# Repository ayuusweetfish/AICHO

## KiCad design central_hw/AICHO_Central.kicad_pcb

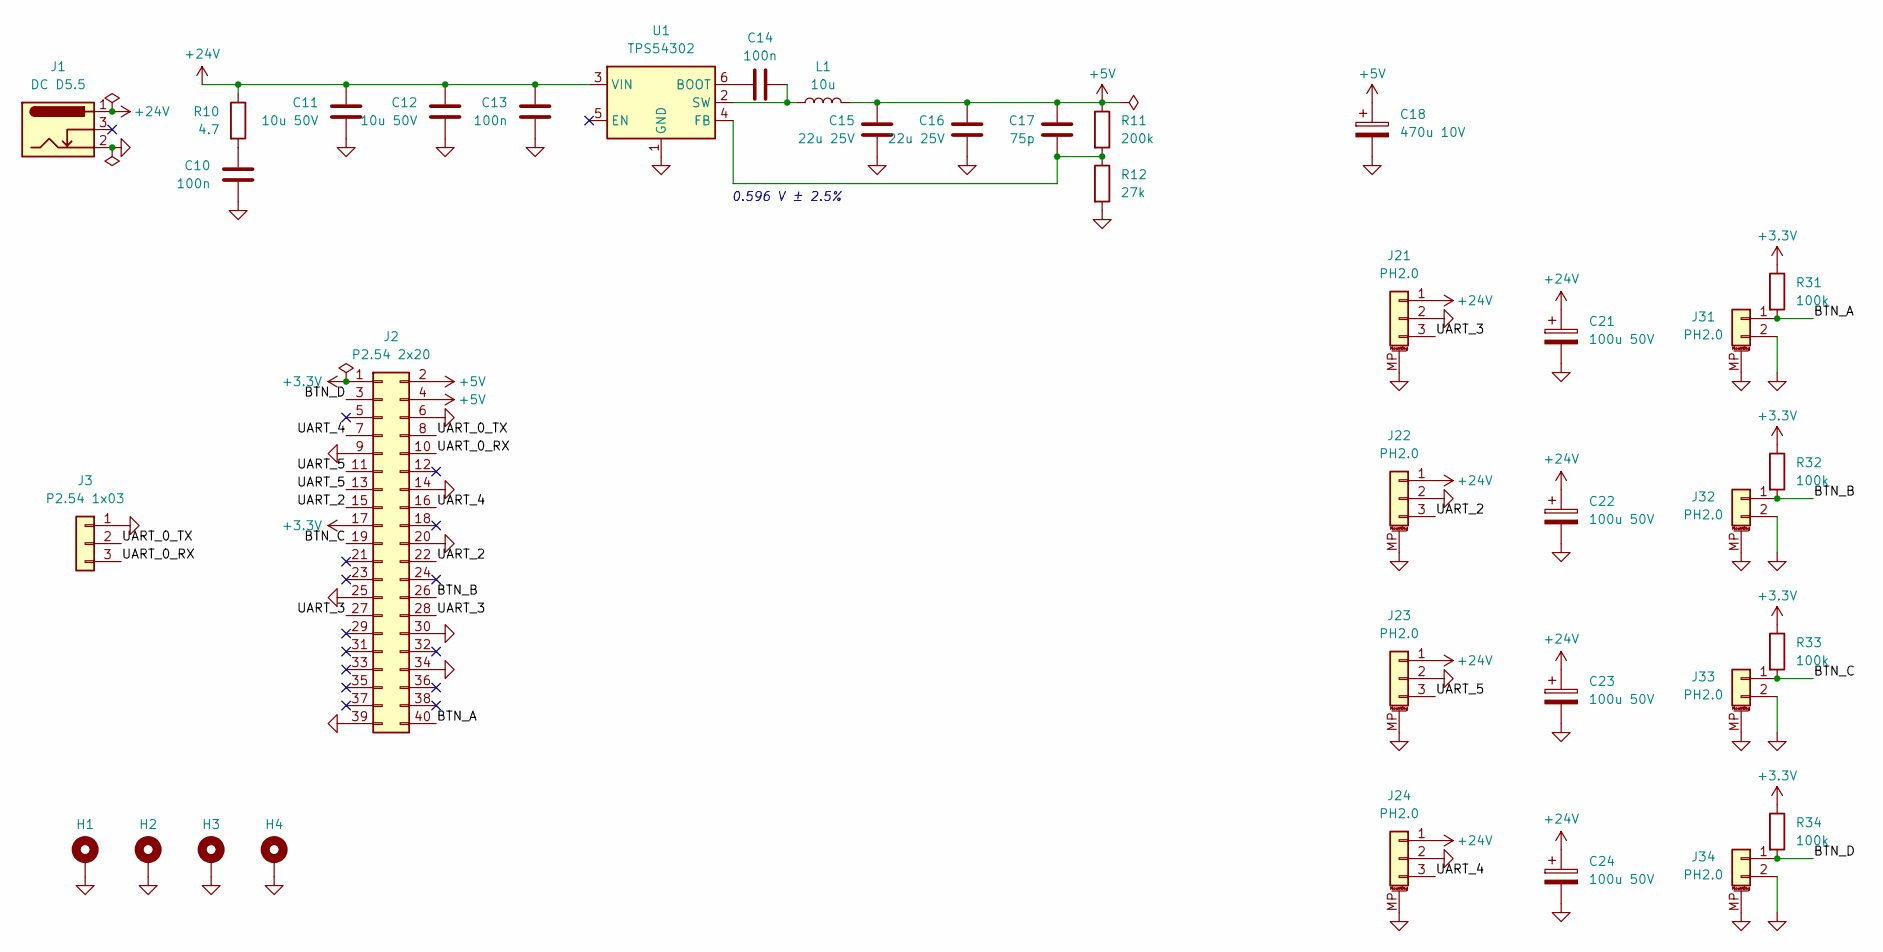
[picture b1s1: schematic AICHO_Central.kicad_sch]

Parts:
C10, C13, C14: 100n; C_0402_1005Metric
C11, C12: 10u 50V; C_0805_2012Metric
C15, C16: 22u 25V; C_0805_2012Metric
C17: 75p; C_0402_1005Metric
C18: 470u 10V; CP_Elec_6.3x7.7; Mfr PN RVT1E221M0607; LCSC PN C696188
C21, C22, C23, C24: 100u 50V; CP_Elec_6.3x7.7; Mfr PN RVT1E221M0607; LCSC PN C696188
H1, H2, H3, H4: MountingHole; MountingHole_2.2mm_M2_Pad_Via
J1: DC D5.5; BarrelJack_Kycon_KLDX-0202-xC_Horizontal
J2: P2.54 2x20; PinHeader_2x20_P2.54mm_Vertical
J3: P2.54 1x03; PinSocket_1x03_P2.54mm_Vertical
J21, J22, J23, J24: PH2.0; JST_PH_S3B-PH-SM4-TB_1x03-1MP_P2.00mm_Horizontal
J31, J32, J33, J34: PH2.0; JST_PH_S2B-PH-SM4-TB_1x02-1MP_P2.00mm_Horizontal
L1: 10u; L_Sunlord_SWPA4030S; Mfr PN SWPA4030S100MT
R10: 4.7; R_0402_1005Metric
R11: 200k; R_0402_1005Metric
R12: 27k; R_0402_1005Metric
R31, R32, R33, R34: 100k; R_0402_1005Metric
U1: TPS54302; SOT-23-6; LCSC PN C311983

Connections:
+3.3V: J2.1, J2.17, R31.1, R32.1, R33.1, R34.1
+5V: C15.1, C16.1, C17.1, C18.1, J2.2, J2.4, L1.2, R11.1
+24V: C11.1, C12.1, C13.1, C21.1, C22.1, C23.1, C24.1, J1.1, J21.1, J22.1, J23.1, J24.1, R10.1, U1.3 (VIN)
/BTN_A: J2.40, J31.1, R31.2
/BTN_B: J2.26, J32.1, R32.2
/BTN_C: J2.19, J33.1, R33.2
/BTN_D: J2.3, J34.1, R34.2
/UART_0_RX: J2.10, J3.3
/UART_0_TX: J2.8, J3.2
/UART_2: J2.15, J2.22, J22.3
/UART_3: J2.27, J2.28, J21.3
/UART_4: J2.7, J2.16, J24.3
/UART_5: J2.11, J2.13, J23.3
GND: C10.2, C11.2, C12.2, C13.2, C15.2, C16.2, C18.2, C21.2, C22.2, C23.2, C24.2, H1.1, H2.1, H3.1, H4.1, J1.2, J2.6, J2.9, J2.14, J2.20, J2.25, J2.30, J2.34, J2.39, J3.1, J21.2, J21.MP (MountPin), J22.2, J22.MP (MountPin), J23.2, J23.MP (MountPin), J24.2, J24.MP (MountPin), J31.2, J31.MP (MountPin), J32.2, J32.MP (MountPin), J33.2, J33.MP (MountPin), J34.2, J34.MP (MountPin), R12.2, U1.1 (GND)
unnamed: C10.1, R10.2
unnamed: C14.1, U1.6 (BOOT)
unnamed: C17.2, R11.2, R12.1, U1.4 (FB)
unnamed: C14.2, L1.1, U1.2 (SW)

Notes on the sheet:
0.596 V ± 2.5%

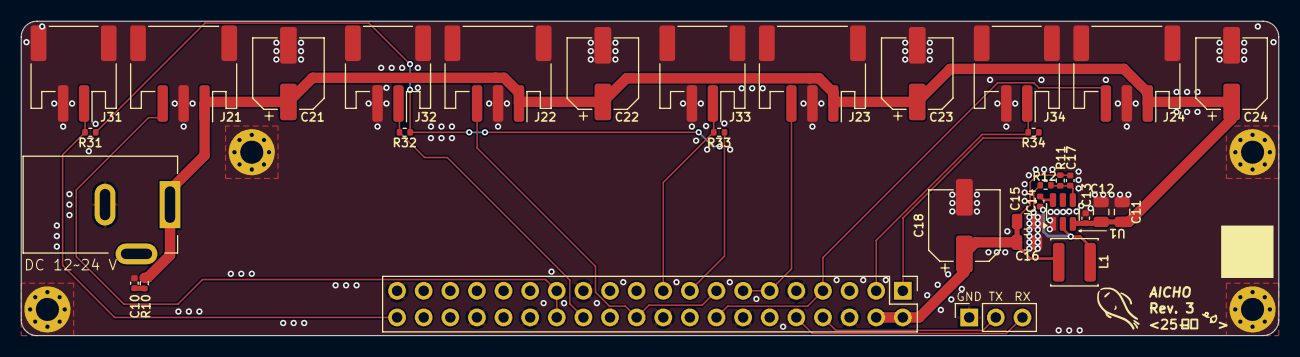
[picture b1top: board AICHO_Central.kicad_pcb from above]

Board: 2 copper layers, 120.0 x 30.0 mm, 37 parts (0 on the bottom side), 18 nets.

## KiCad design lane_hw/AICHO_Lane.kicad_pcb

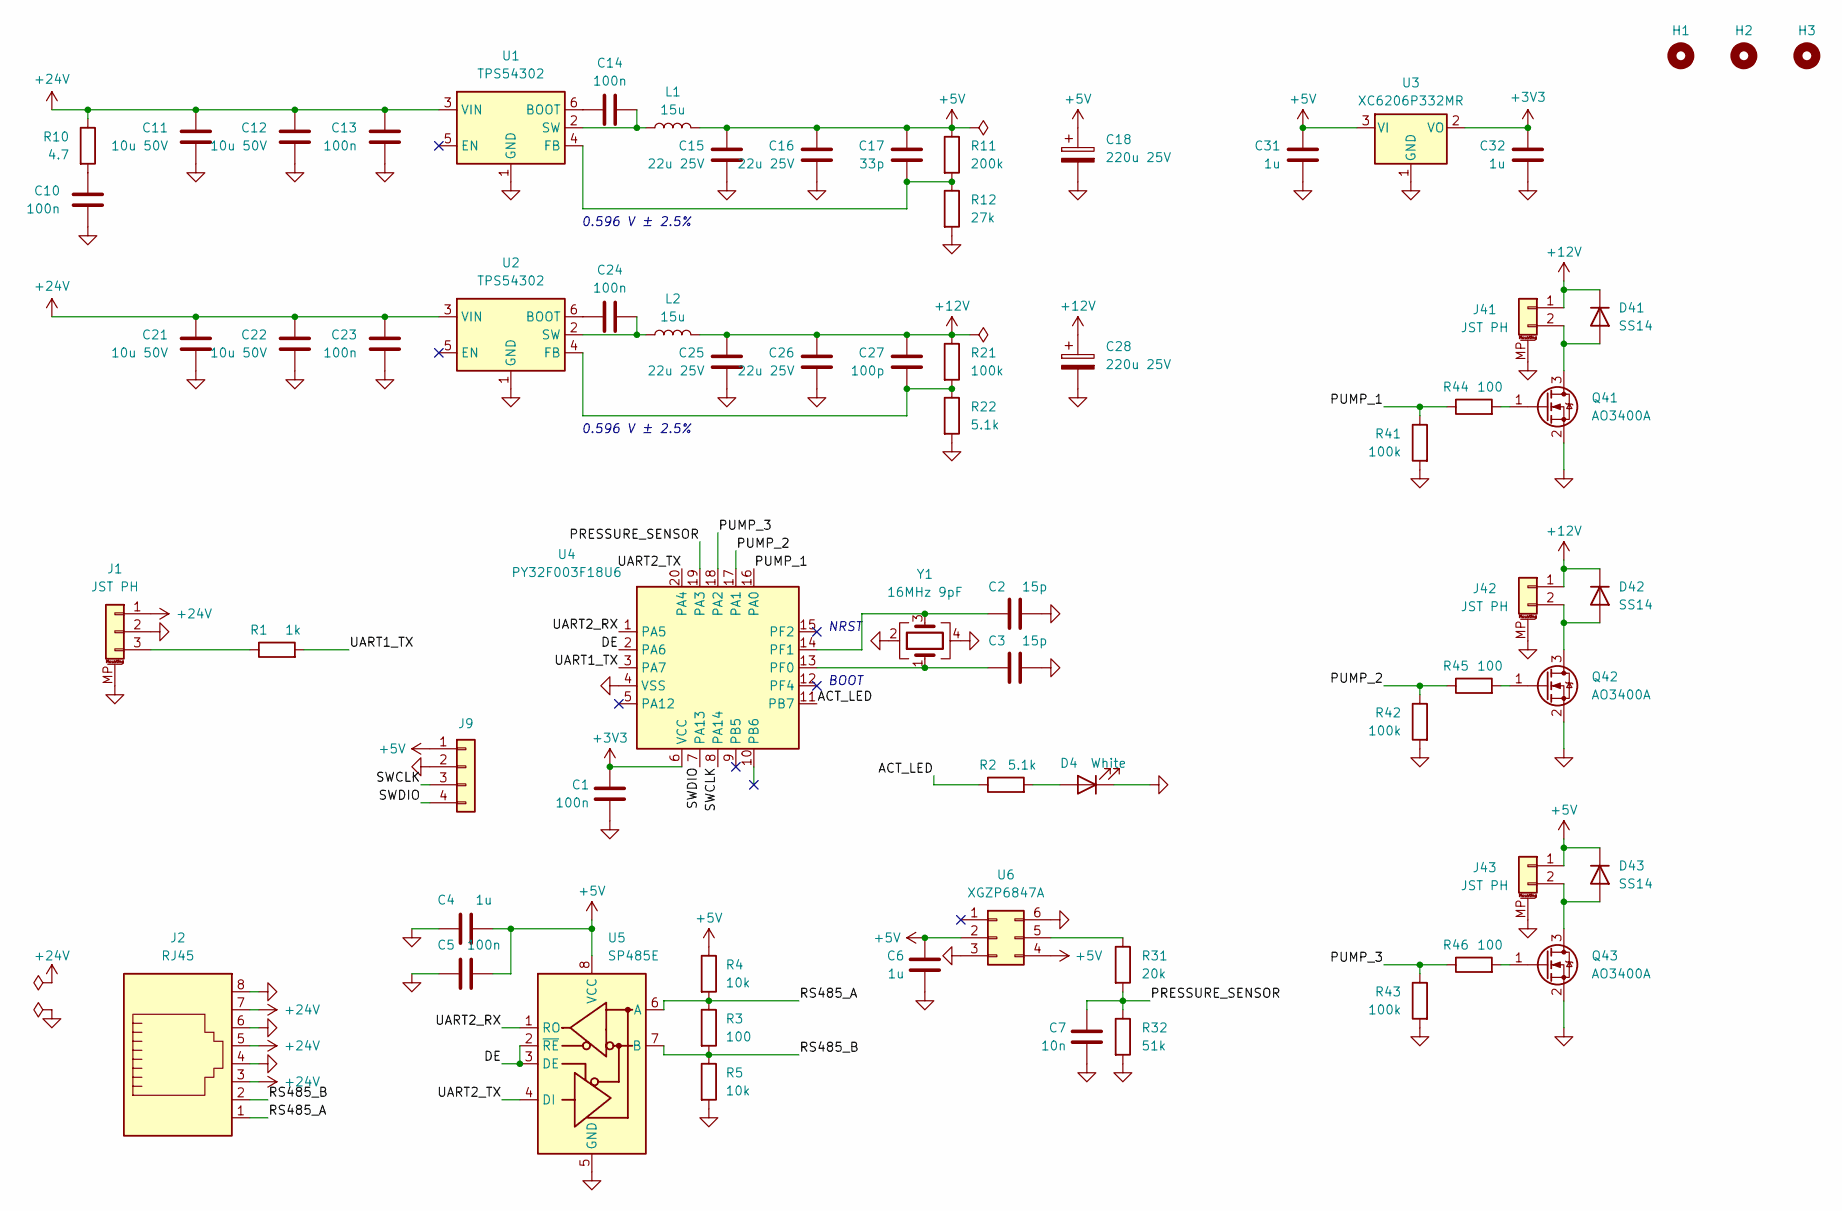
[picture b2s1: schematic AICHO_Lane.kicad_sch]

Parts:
C1, C5, C10, C13, C14, C23, C24: 100n; C_0402_1005Metric
C2, C3: 15p; C_0402_1005Metric
C4, C6, C31, C32: 1u; C_0402_1005Metric
C7: 10n; C_0402_1005Metric
C11, C12, C21, C22: 10u 50V; C_0805_2012Metric
C15, C16, C25, C26: 22u 25V; C_0805_2012Metric
C17: 33p; C_0402_1005Metric
C18, C28: 220u 25V; CP_Elec_6.3x7.7; Mfr PN RVT1E221M0607; LCSC PN C696188
C27: 100p; C_0402_1005Metric
D4: White; LED_0603_1608Metric
D41, D42, D43: SS14; D_SMA
H1, H2, H3: MountingHole; MountingHole_2.2mm_M2
J1: JST PH; JST_PH_S3B-PH-SM4-TB_1x03-1MP_P2.00mm_Horizontal; LCSC PN C7433649
J2: RJ45; RJ45_OST_PJ012-8P8CX_Vertical
J9: Conn_01x04; TestPoints_1x04_P2.00
J41, J42, J43: JST PH; JST_PH_S2B-PH-SM4-TB_1x02-1MP_P2.00mm_Horizontal; LCSC PN C7433648
L1, L2: 15u; L_Sunlord_SWPA5040S; Mfr PN PRS5040-150MT; LCSC PN C2961339
Q41, Q42, Q43: AO3400A; SOT-23
R1: 1k; R_0402_1005Metric
R2, R22: 5.1k; R_0402_1005Metric
R3, R44, R45, R46: 100; R_0402_1005Metric
R4, R5: 10k; R_0402_1005Metric
R10: 4.7; R_0402_1005Metric
R11: 200k; R_0402_1005Metric
R12: 27k; R_0402_1005Metric
R21, R41, R42, R43: 100k; R_0402_1005Metric
R31: 20k; R_0402_1005Metric
R32: 51k; R_0402_1005Metric
U1, U2: TPS54302; SOT-23-6; LCSC PN C311983
U3: XC6206P332MR; SOT-23-3; LCSC PN C5446
U4: PY32F003F18U6; QFN-20-1EP_3x3mm_P0.4mm_EP1.65x1.65mm; LCSC PN C7422665
U5: SP485E; SOIC-8_3.9x4.9mm_P1.27mm; LCSC PN C6855
U6: XGZP6847A
Y1: 16MHz 9pF; Crystal_SMD_3225-4Pin_3.2x2.5mm; Mfr PN X322516MLB4SI; LCSC PN C13738

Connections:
+3V3: C1.1, C32.1, U3.2 (VO), U4.6 (VCC)
+5V: C4.2, C5.2, C6.1, C15.1, C16.1, C17.1, C18.1, C31.1, D43.1 (K), J9.1, J43.1, L1.2, R4.1, R11.1, U3.3 (VI), U5.8 (VCC), U6.2, U6.4
+12V: C25.1, C26.1, C27.1, C28.1, D41.1 (K), D42.1 (K), J41.1, J42.1, L2.2, R21.1
+24V: C11.1, C12.1, C13.1, C21.1, C22.1, C23.1, J1.1, J2.3, J2.5, J2.7, R10.1, U1.3 (VIN), U2.3 (VIN)
/ACT_LED: R2.1, U4.11 (PB7)
/DE: U4.2 (PA6), U5.2 (~RE), U5.3 (DE)
/PRESSURE_SENSOR: C7.1, R31.2, R32.1, U4.19 (PA3)
/PUMP_1: R41.1, R44.1, U4.16 (PA0)
/PUMP_2: R42.1, R45.1, U4.17 (PA1)
/PUMP_3: R43.1, R46.1, U4.18 (PA2)
/RS485_A: J2.1, R3.1, R4.2, U5.6 (A)
/RS485_B: J2.2, R3.2, R5.1, U5.7 (B)
/SWCLK: J9.3, U4.8 (PA14)
/SWDIO: J9.4, U4.7 (PA13)
/UART1_TX: R1.2, U4.3 (PA7)
/UART2_RX: U4.1 (PA5), U5.1 (RO)
/UART2_TX: U4.20 (PA4), U5.4 (DI)
GND: C1.2, C2.2, C3.2, C4.1, C5.1, C6.2, C7.2, C10.2, C11.2, C12.2, C13.2, C15.2, C16.2, C18.2, C21.2, C22.2, C23.2, C25.2, C26.2, C28.2, C31.2, C32.2, D4.1 (K), J1.2, J1.MP (MountPin), J2.4, J2.6, J2.8, J9.2, J41.MP (MountPin), J42.MP (MountPin), J43.MP (MountPin), Q41.2 (S), Q42.2 (S), Q43.2 (S), R5.2, R12.2, R22.2, R32.2, R41.2, R42.2, R43.2, U1.1 (GND), U2.1 (GND), U3.1 (GND), U4.4 (VSS), U4.21 (PAD), U5.5 (GND), U6.3, U6.6, Y1.2, Y1.4
unnamed: C10.1, R10.2
unnamed: D4.2 (A), R2.2
unnamed: D41.2 (A), J41.2, Q41.3 (D)
unnamed: D42.2 (A), J42.2, Q42.3 (D)
unnamed: D43.2 (A), J43.2, Q43.3 (D)
unnamed: J1.3, R1.1
unnamed: Q41.1 (G), R44.2
unnamed: Q42.1 (G), R45.2
unnamed: Q43.1 (G), R46.2
unnamed: C14.1, U1.6 (BOOT)
unnamed: C17.2, R11.2, R12.1, U1.4 (FB)
unnamed: C14.2, L1.1, U1.2 (SW)
unnamed: C24.1, U2.6 (BOOT)
unnamed: C27.2, R21.2, R22.1, U2.4 (FB)
unnamed: C24.2, L2.1, U2.2 (SW)
unnamed: C3.1, U4.13 (PF0), Y1.1
unnamed: C2.1, U4.14 (PF1), Y1.3
unnamed: R31.1, U6.5

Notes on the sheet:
BOOT
NRST
0.596 V ± 2.5%

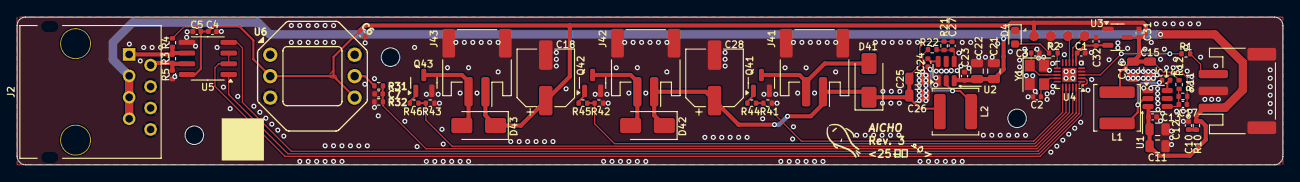
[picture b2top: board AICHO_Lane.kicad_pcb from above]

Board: 2 copper layers, 150.0 x 17.5 mm, 69 parts (0 on the bottom side), 36 nets.

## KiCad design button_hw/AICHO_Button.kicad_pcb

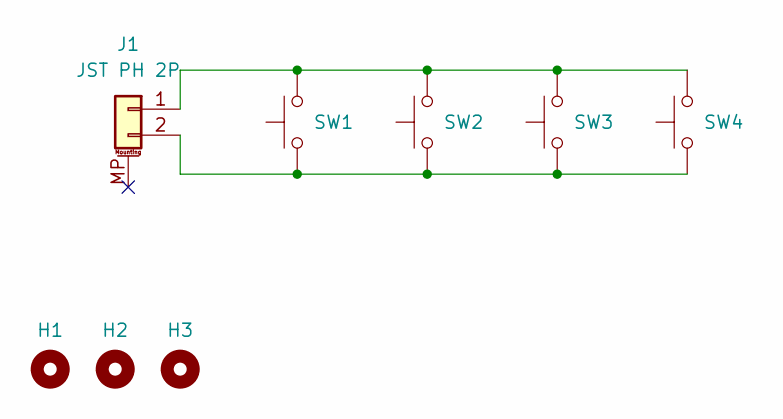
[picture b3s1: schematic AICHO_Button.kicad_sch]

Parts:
H1, H2, H3: MountingHole; MountingHole_2mm
J1: JST PH 2P; JST_PH_S2B-PH-SM4-TB_1x02-1MP_P2.00mm_Horizontal
SW1, SW2, SW3, SW4: SW_Push; SW_Cherry_MX_1.00u_Plate

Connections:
unnamed: J1.1, SW1.1, SW2.1, SW3.1, SW4.1
unnamed: J1.2, SW1.2, SW2.2, SW3.2, SW4.2

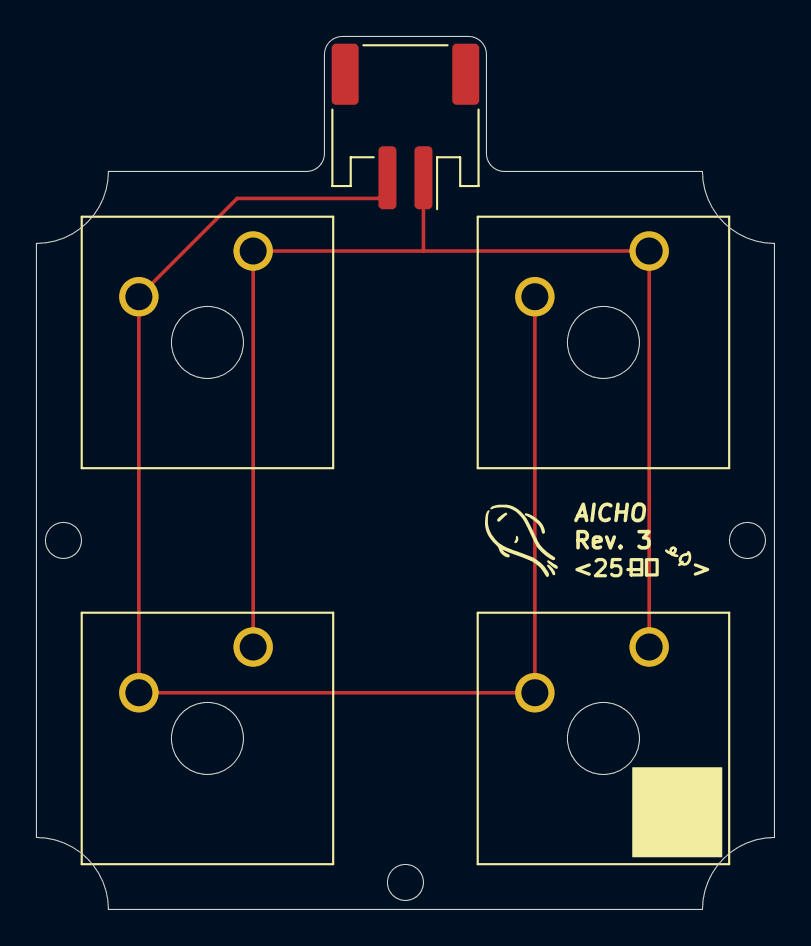
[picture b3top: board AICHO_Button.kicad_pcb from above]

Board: 2 copper layers, 41.0 x 48.5 mm, 8 parts (0 on the bottom side), 2 nets.

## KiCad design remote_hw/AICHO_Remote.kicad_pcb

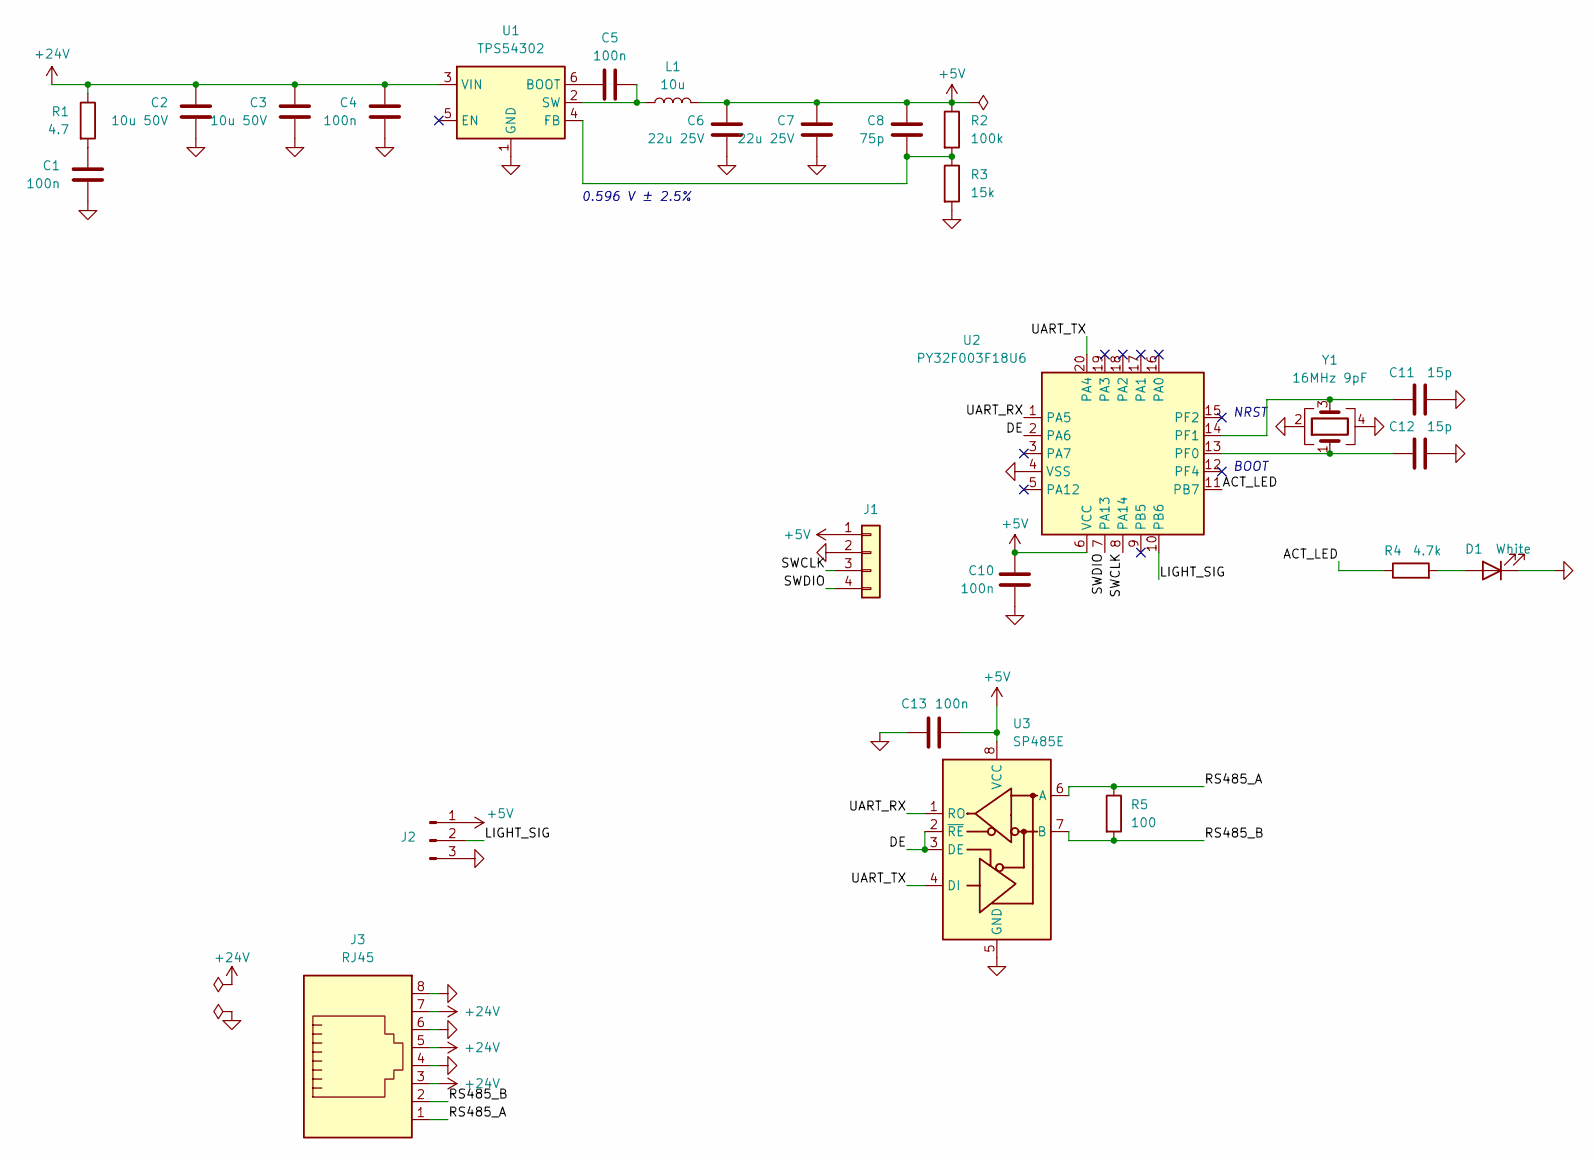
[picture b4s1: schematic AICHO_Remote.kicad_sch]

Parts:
C1, C4, C5, C10, C13: 100n; C_0402_1005Metric
C2, C3: 10u 50V; C_0805_2012Metric
C6, C7: 22u 25V; C_0805_2012Metric
C8: 75p; C_0402_1005Metric
C11, C12: 15p; C_0402_1005Metric
D1: White; LED_0603_1608Metric
J1: Conn_01x04; TestPoints_1x04_P2.00
J2: Conn_01x03_Pin; PinHeader_1x03_P2.54mm_Vertical
J3: RJ45; RJ45_OST_PJ012-8P8CX_Vertical
L1: 10u; L_Sunlord_SWPA4030S; Mfr PN SWPA4030S100MT; LCSC PN C38117
R1: 4.7; R_0402_1005Metric
R2: 100k; R_0402_1005Metric
R3: 15k; R_0402_1005Metric
R4: 4.7k; R_0402_1005Metric
R5: 100; R_0402_1005Metric
U1: TPS54302; SOT-23-6; LCSC PN C311983
U2: PY32F003F18U6; QFN-20-1EP_3x3mm_P0.4mm_EP1.65x1.65mm; LCSC PN C7422665
U3: SP485E; SOIC-8_3.9x4.9mm_P1.27mm; LCSC PN C6855
Y1: 16MHz 9pF; Crystal_SMD_3225-4Pin_3.2x2.5mm; Mfr PN X322516MLB4SI; LCSC PN C13738

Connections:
+5V: C6.1, C7.1, C8.1, C10.1, C13.2, J1.1, J2.1, L1.2, R2.1, U2.6 (VCC), U3.8 (VCC)
+24V: C2.1, C3.1, C4.1, J3.3, J3.5, J3.7, R1.1, U1.3 (VIN)
/ACT_LED: R4.1, U2.11 (PB7)
/DE: U2.2 (PA6), U3.2 (~RE), U3.3 (DE)
/LIGHT_SIG: J2.2, U2.10 (PB6)
/RS485_A: J3.1, R5.1, U3.6 (A)
/RS485_B: J3.2, R5.2, U3.7 (B)
/SWCLK: J1.3, U2.8 (PA14)
/SWDIO: J1.4, U2.7 (PA13)
/UART_RX: U2.1 (PA5), U3.1 (RO)
/UART_TX: U2.20 (PA4), U3.4 (DI)
GND: C1.2, C2.2, C3.2, C4.2, C6.2, C7.2, C10.2, C11.2, C12.2, C13.1, D1.1 (K), J1.2, J2.3, J3.4, J3.6, J3.8, R3.2, U1.1 (GND), U2.4 (VSS), U2.21 (PAD), U3.5 (GND), Y1.2, Y1.4
unnamed: C1.1, R1.2
unnamed: D1.2 (A), R4.2
unnamed: C5.1, U1.6 (BOOT)
unnamed: C8.2, R2.2, R3.1, U1.4 (FB)
unnamed: C5.2, L1.1, U1.2 (SW)
unnamed: C12.1, U2.13 (PF0), Y1.1
unnamed: C11.1, U2.14 (PF1), Y1.3

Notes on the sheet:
BOOT
NRST
0.596 V ± 2.5%

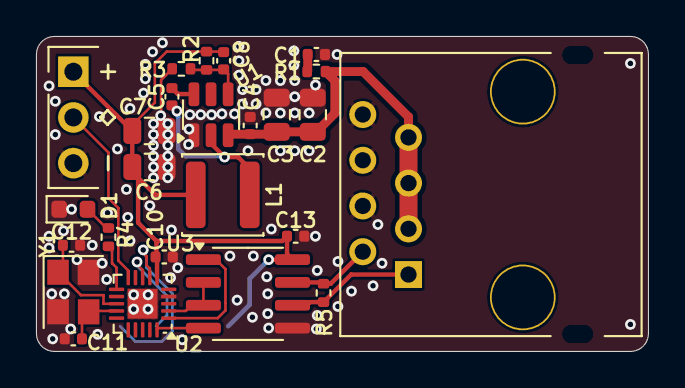
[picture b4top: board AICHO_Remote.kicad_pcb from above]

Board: 2 copper layers, 34.0 x 17.5 mm, 26 parts (1 on the bottom side), 19 nets.

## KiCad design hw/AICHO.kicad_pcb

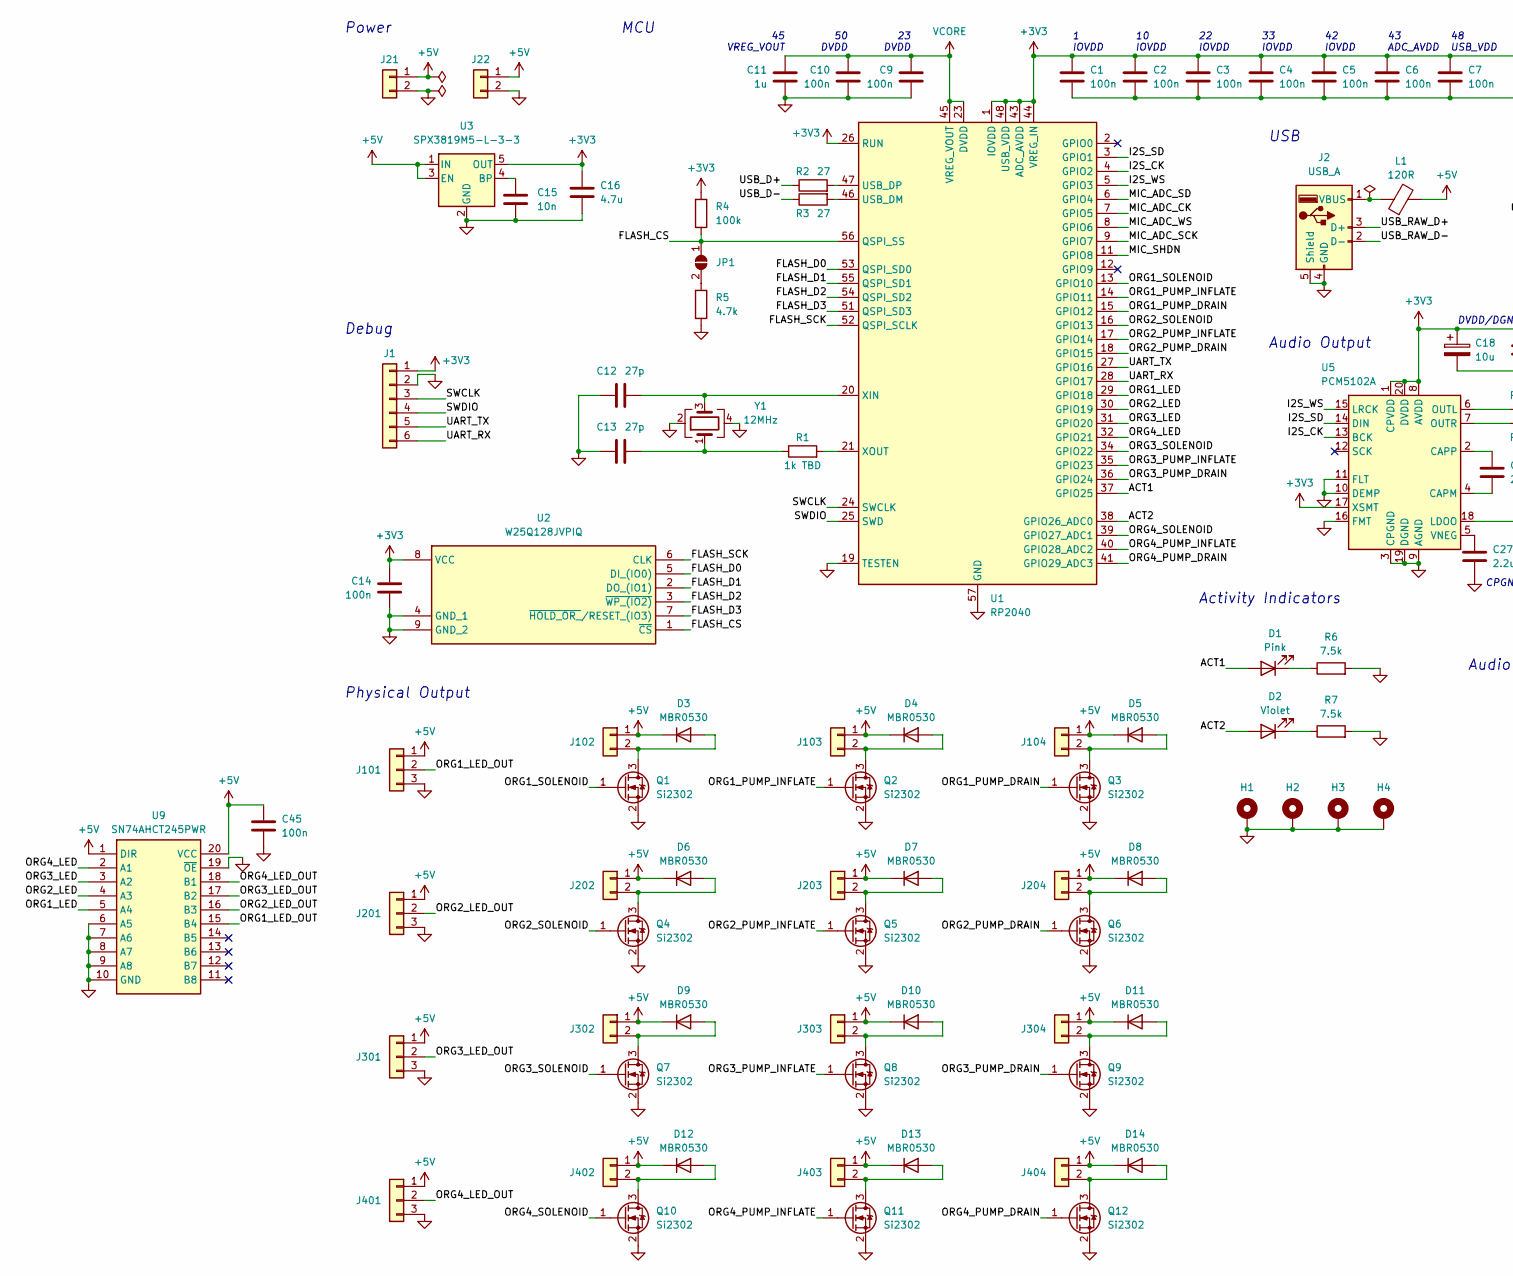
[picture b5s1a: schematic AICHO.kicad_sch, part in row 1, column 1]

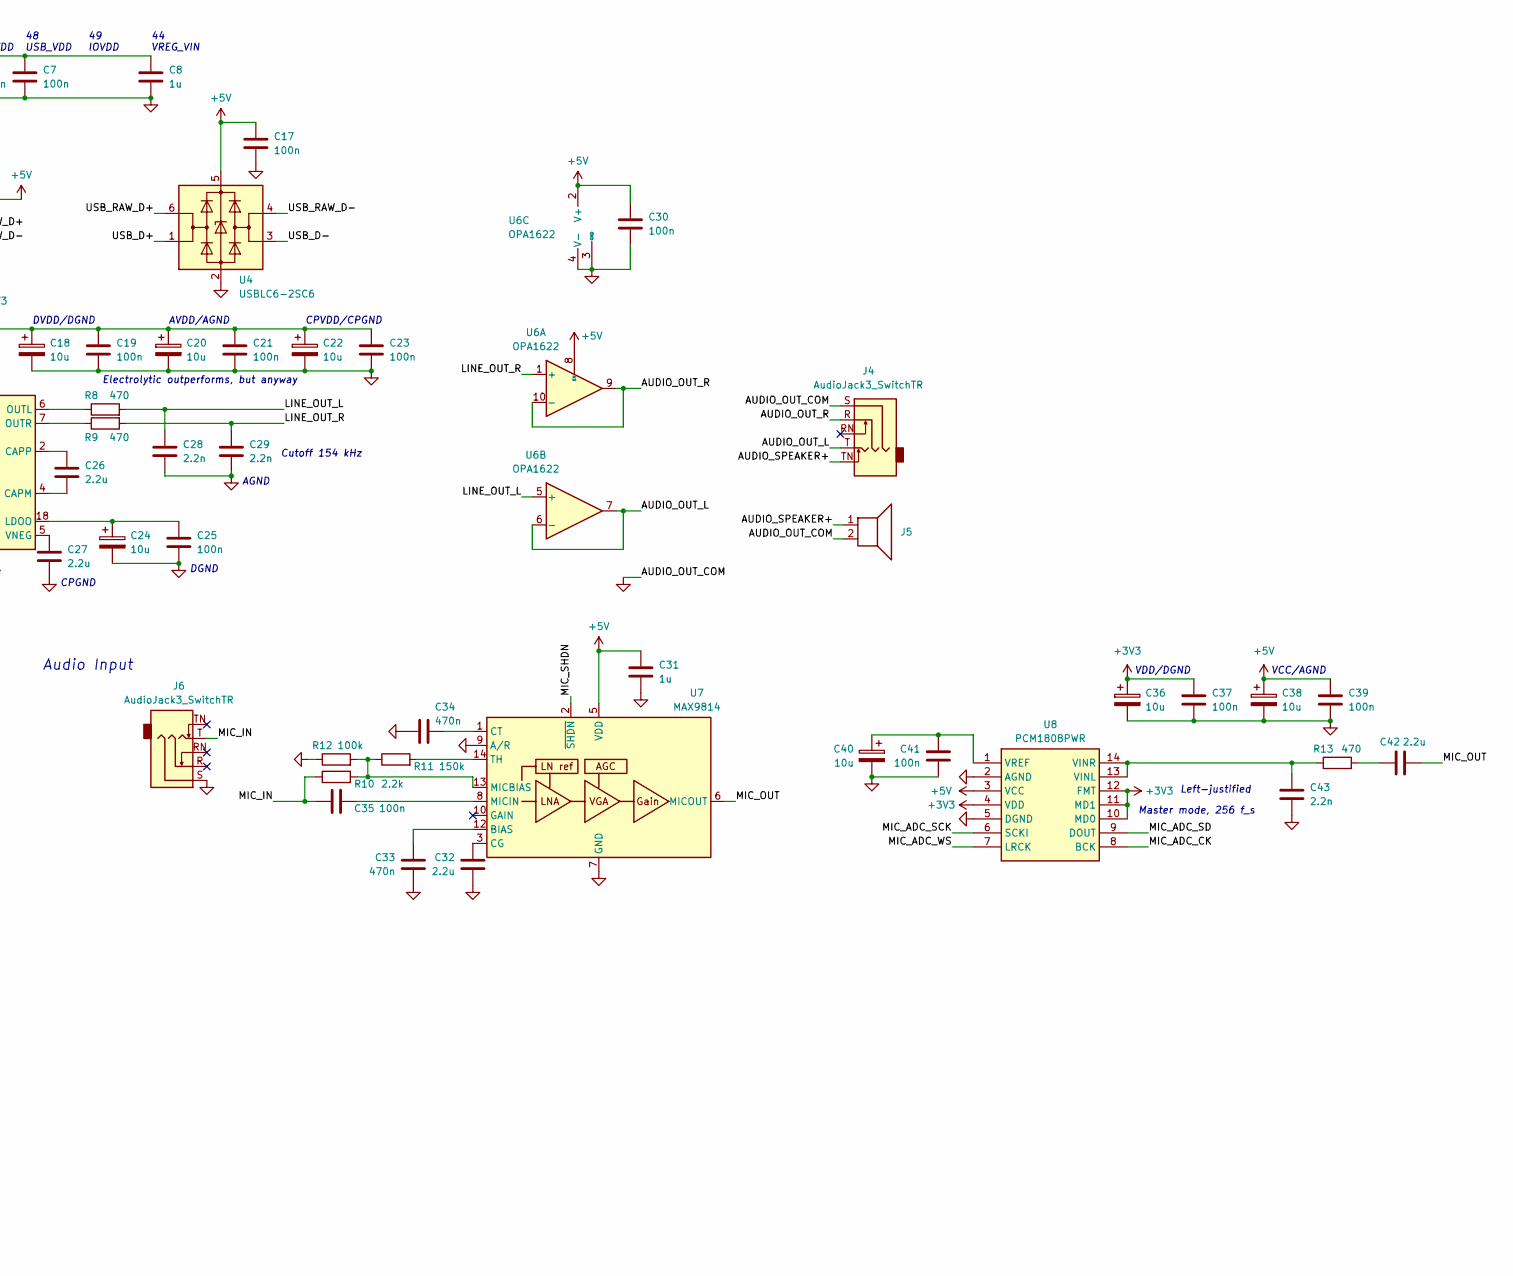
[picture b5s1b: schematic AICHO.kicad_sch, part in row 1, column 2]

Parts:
C1, C2, C3, C4, C5, C6, C7, C9, C10, C14, C17, C19, C21, C23, C25, C30, C35, C37, C39, C41, C45: 100n; C_0402_1005Metric
C8, C11, C31: 1u; C_0402_1005Metric
C12, C13: 27p; C_0402_1005Metric
C15: 10n; C_0603_1608Metric
C16: 4.7u; C_0603_1608Metric
C18, C20, C22, C24, C36, C38, C40: 10u; C_0603_1608Metric
C26, C27, C32, C42: 2.2u; C_0402_1005Metric
C28, C29, C43: 2.2n; C_0402_1005Metric
C33, C34: 470n; C_0402_1005Metric
D1: Pink; LED_0603_1608Metric
D2: Violet; LED_0603_1608Metric
D3, D4, D5, D6, D7, D8, D9, D10, D11, D12, D13, D14: MBR0530; D_SOD-123
H1, H2, H3, H4: MountingHole_Pad; MountingHole_2.5mm_Pad_Via
J1: Conn_01x06; TestPoints_1x06_P2.0
J2: USB_A; USB_A_CNCTech_1001-011-01101_Horizontal
J4, J6: AudioJack3_SwitchTR; Jack_3.5mm_CUI_SJ1-3525N_Horizontal
J5: Speaker; PinHeader_1x02_P2.54mm_Vertical
J21, J22, J102, J103, J104, J202, J203, J204, J302, J303, J304, J402, J403, J404: Conn_01x02; PinHeader_1x02_P2.54mm_Vertical
J101, J201, J301, J401: Conn_01x03; PinHeader_1x03_P2.54mm_Vertical
JP1: SolderJumper_2_Open; SolderJumper-2_P1.3mm_Open_RoundedPad1.0x1.5mm
L1: 120R; L_0805_2012Metric
Q1, Q2, Q3, Q4, Q5, Q6, Q7, Q8, Q9, Q10, Q11, Q12: Si2302; SOT-23
R1: 1k TBD; R_0603_1608Metric
R2, R3: 27; R_0603_1608Metric
R4: 100k; R_0603_1608Metric
R5: 4.7k; R_0603_1608Metric
R6, R7: 7.5k; R_0603_1608Metric
R8, R9, R13: 470; R_0402_1005Metric
R10: 2.2k; R_0402_1005Metric
R11: 150k; R_0402_1005Metric
R12: 100k; R_0402_1005Metric
U1: RP2040; QFN-56-1EP_7x7mm_P0.4mm_EP3.2x3.2mm
U2: W25Q128JVPIQ; SON127P600X500X80-9N-D; Manufacturer_Part_Number W25Q128JVPIQ; Mouser Part Number 454-W25Q128JVPIQ
U3: SPX3819M5-L-3-3; SOT-23-5
U4: USBLC6-2SC6; SOT-23-6
U5: PCM5102A; TSSOP-20_4.4x6.5mm_P0.65mm
U6: OPA1622; Texas_S-PVSON-N10
U7: MAX9814; DFN-14-1EP_3x3mm_P0.4mm_EP1.78x2.35mm
U8: PCM1808PWR; Manufacturer_Part_Number PCM1808PWR; Mouser Part Number 595-PCM1808PWR
U9: SN74AHCT245PWR; SOP65P640X120-20N; Manufacturer_Part_Number SN74AHCT245PWR; Mouser Part Number 595-SN74AHCT245PWR
Y1: 12MHz; Crystal_SMD_3225-4Pin_3.2x2.5mm

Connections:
+3V3: C1.1, C2.1, C3.1, C4.1, C5.1, C6.1, C7.1, C8.1, C14.1, C16.1, C18.1, C19.1, C20.1, C21.1, C22.1, C23.1, C36.1, C37.1, J1.1, R4.2, U1.1 (IOVDD), U1.10 (IOVDD), U1.22 (IOVDD), U1.26 (RUN), U1.33 (IOVDD), U1.42 (IOVDD), U1.43 (ADC_AVDD), U1.44 (VREG_IN), U1.48 (USB_VDD), U1.49 (IOVDD), U2.8 (VCC), U3.5 (OUT), U5.1 (CPVDD), U5.8 (AVDD), U5.17 (XSMT), U5.20 (DVDD), U8.4 (VDD), U8.10 (MD0), U8.11 (MD1), U8.12 (FMT)
+5V: C17.1, C30.1, C31.1, C38.1, C39.1, C45.1, D3.1 (K), D4.1 (K), D5.1 (K), D6.1 (K), D7.1 (K), D8.1 (K), D9.1 (K), D10.1 (K), D11.1 (K), D12.1 (K), D13.1 (K), D14.1 (K), J21.1, J22.1, J101.1, J102.1, J103.1, J104.1, J201.1, J202.1, J203.1, J204.1, J301.1, J302.1, J303.1, J304.1, J401.1, J402.1, J403.1, J404.1, L1.2, U3.1 (IN), U3.3 (EN), U4.5 (VBUS), U6.2 (V+), U6.8 (EN), U7.5 (VDD), U8.3 (VCC), U9.1 (DIR), U9.20 (VCC)
/ACT1: D1.2 (A), U1.37 (GPIO25)
/ACT2: D2.2 (A), U1.38 (GPIO26_ADC0)
/AUDIO_OUT_L: J4.T, U6.6 (-), U6.7
/AUDIO_OUT_R: J4.R, U6.9, U6.10 (-)
/AUDIO_SPEAKER+: J4.TN, J5.1
/FLASH_CS: JP1.1 (A), R4.1, U1.56 (QSPI_SS), U2.1 (~CS)
/FLASH_D0: U1.53 (QSPI_SD0), U2.5 (DI_(IO0))
/FLASH_D1: U1.55 (QSPI_SD1), U2.2 (DO_(IO1))
/FLASH_D2: U1.54 (QSPI_SD2), U2.3 (~WP_(IO2))
/FLASH_D3: U1.51 (QSPI_SD3), U2.7 (~HOLD_OR_/RESET_(IO3))
/FLASH_SCK: U1.52 (QSPI_SCLK), U2.6 (CLK)
/I2S_CK: U1.4 (GPIO2), U5.13 (BCK)
/I2S_SD: U1.3 (GPIO1), U5.14 (DIN)
/I2S_WS: U1.5 (GPIO3), U5.15 (LRCK)
/LINE_OUT_L: C28.1, R8.2, U6.5 (+)
/LINE_OUT_R: C29.1, R9.2, U6.1 (+)
/MIC_ADC_CK: U1.7 (GPIO5), U8.8 (BCK)
/MIC_ADC_SCK: U1.9 (GPIO7), U8.6 (SCKI)
/MIC_ADC_SD: U1.6 (GPIO4), U8.9 (DOUT)
/MIC_ADC_WS: U1.8 (GPIO6), U8.7 (LRCK)
/MIC_IN: C35.1, J6.T, R10.1
/MIC_OUT: C42.2, U7.6 (MICOUT)
/MIC_SHDN: U1.11 (GPIO8), U7.2 (~SHDN)
/ORG1_LED: U1.29 (GPIO18), U9.5 (A4)
/ORG1_LED_OUT: J101.2, U9.15 (B4)
/ORG1_PUMP_DRAIN: Q3.1 (G), U1.15 (GPIO12)
/ORG1_PUMP_INFLATE: Q2.1 (G), U1.14 (GPIO11)
/ORG1_SOLENOID: Q1.1 (G), U1.13 (GPIO10)
/ORG2_LED: U1.30 (GPIO19), U9.4 (A3)
/ORG2_LED_OUT: J201.2, U9.16 (B3)
/ORG2_PUMP_DRAIN: Q6.1 (G), U1.18 (GPIO15)
/ORG2_PUMP_INFLATE: Q5.1 (G), U1.17 (GPIO14)
/ORG2_SOLENOID: Q4.1 (G), U1.16 (GPIO13)
/ORG3_LED: U1.31 (GPIO20), U9.3 (A2)
/ORG3_LED_OUT: J301.2, U9.17 (B2)
/ORG3_PUMP_DRAIN: Q9.1 (G), U1.36 (GPIO24)
/ORG3_PUMP_INFLATE: Q8.1 (G), U1.35 (GPIO23)
/ORG3_SOLENOID: Q7.1 (G), U1.34 (GPIO22)
/ORG4_LED: U1.32 (GPIO21), U9.2 (A1)
/ORG4_LED_OUT: J401.2, U9.18 (B1)
/ORG4_PUMP_DRAIN: Q12.1 (G), U1.41 (GPIO29_ADC3)
/ORG4_PUMP_INFLATE: Q11.1 (G), U1.40 (GPIO28_ADC2)
/ORG4_SOLENOID: Q10.1 (G), U1.39 (GPIO27_ADC1)
/SWCLK: J1.3, U1.24 (SWCLK)
/SWDIO: J1.4, U1.25 (SWD)
/UART_RX: J1.6, U1.28 (GPIO17)
/UART_TX: J1.5, U1.27 (GPIO16)
/USB_D+: R2.1, U4.1 (I/O1)
/USB_D-: R3.1, U4.3 (I/O2)
/USB_RAW_D+: J2.3 (D+), U4.6 (I/O1)
/USB_RAW_D-: J2.2 (D-), U4.4 (I/O2)
GND: C1.2, C2.2, C3.2, C4.2, C5.2, C6.2, C7.2, C8.2, C9.2, C10.2, C11.2, C12.1, C13.1, C14.2, C15.2, C16.2, C17.2, C18.2, C19.2, C20.2, C21.2, C22.2, C23.2, C24.2, C25.2, C27.2, C28.2, C29.2, C30.2, C31.2, C32.2, C33.2, C34.2, C36.2, C37.2, C38.2, C39.2, C40.2, C41.2, C43.2, C45.2, H1.1, H2.1, H3.1, H4.1, J1.2, J2.4 (GND), J2.5 (Shield), J4.S, J5.2, J6.S, J21.2, J22.2, J101.3, J201.3, J301.3, J401.3, Q1.2 (S), Q2.2 (S), Q3.2 (S), Q4.2 (S), Q5.2 (S), Q6.2 (S), Q7.2 (S), Q8.2 (S), Q9.2 (S), Q10.2 (S), Q11.2 (S), Q12.2 (S), R5.1, R6.2, R7.2, R12.1, U1.19 (TESTEN), U1.57 (GND), U2.4 (GND_1), U2.9 (GND_2), U3.2 (GND), U4.2 (GND), U5.3 (CPGND), U5.9 (AGND), U5.10 (DEMP), U5.11 (FLT), U5.16 (FMT), U5.19 (DGND), U6.3 (GND), U6.4 (V-), U6.11 (V-), U7.4 (GND), U7.7 (GND), U7.9 (A/R), U7.11 (GND), U7.15 (GND), U8.2 (AGND), U8.5 (DGND), U9.6 (A5), U9.7 (A6), U9.8 (A7), U9.9 (A8), U9.10 (GND), U9.19 (~OE), Y1.2, Y1.4
unnamed: C13.2, R1.1, Y1.1
unnamed: C42.1, R13.2
unnamed: D1.1 (K), R6.1
unnamed: D2.1 (K), R7.1
unnamed: D3.2 (A), J102.2, Q1.3 (D)
unnamed: D4.2 (A), J103.2, Q2.3 (D)
unnamed: D5.2 (A), J104.2, Q3.3 (D)
unnamed: D6.2 (A), J202.2, Q4.3 (D)
unnamed: D7.2 (A), J203.2, Q5.3 (D)
unnamed: D8.2 (A), J204.2, Q6.3 (D)
unnamed: D9.2 (A), J302.2, Q7.3 (D)
unnamed: D10.2 (A), J303.2, Q8.3 (D)
unnamed: D11.2 (A), J304.2, Q9.3 (D)
unnamed: D12.2 (A), J402.2, Q10.3 (D)
unnamed: D13.2 (A), J403.2, Q11.3 (D)
unnamed: D14.2 (A), J404.2, Q12.3 (D)
unnamed: J2.1 (VBUS), L1.1
unnamed: JP1.2 (B), R5.2
unnamed: R3.2, U1.46 (USB_DM)
unnamed: R2.2, U1.47 (USB_DP)
unnamed: C12.2, U1.20 (XIN), Y1.3
unnamed: R1.2, U1.21 (XOUT)
unnamed: C15.1, U3.4 (BP)
unnamed: C26.2, U5.4 (CAPM)
unnamed: C26.1, U5.2 (CAPP)
unnamed: C24.1, C25.1, U5.18 (LDOO)
unnamed: R8.1, U5.6 (OUTL)
unnamed: R9.1, U5.7 (OUTR)
unnamed: C27.1, U5.5 (VNEG)
unnamed: C33.1, U7.12 (BIAS)
unnamed: C32.1, U7.3 (CG)
unnamed: C34.1, U7.1 (CT)
unnamed: R10.2, R11.1, R12.2, U7.13 (MICBIAS)
unnamed: C35.2, U7.8 (MICIN)
unnamed: R11.2, U7.14 (TH)
unnamed: C43.1, R13.1, U8.13 (VINL), U8.14 (VINR)
unnamed: C40.1, C41.1, U8.1 (VREF)
VCORE: C9.1, C10.1, C11.1, U1.23 (DVDD), U1.45 (VREG_VOUT), U1.50 (DVDD)

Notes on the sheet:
Power
AVDD/AGND
33 IOVDD
1 IOVDD
48 USB_VDD
Debug
22 IOVDD
42 IOVDD
AGND
USB
VDD/DGND
CPVDD/CPGND
Electrolytic outperforms, but anyway
50 DVDD
44 VREG_VIN
DVDD/DGND
49 IOVDD
Physical Output
Audio Output
Left-justified
45 VREG_VOUT
Activity Indicators
VCC/AGND
DGND
23 DVDD
Cutoff 154 kHz
10 IOVDD
CPGND
43 ADC_AVDD
Master mode, 256 f_s
MCU
Audio Input

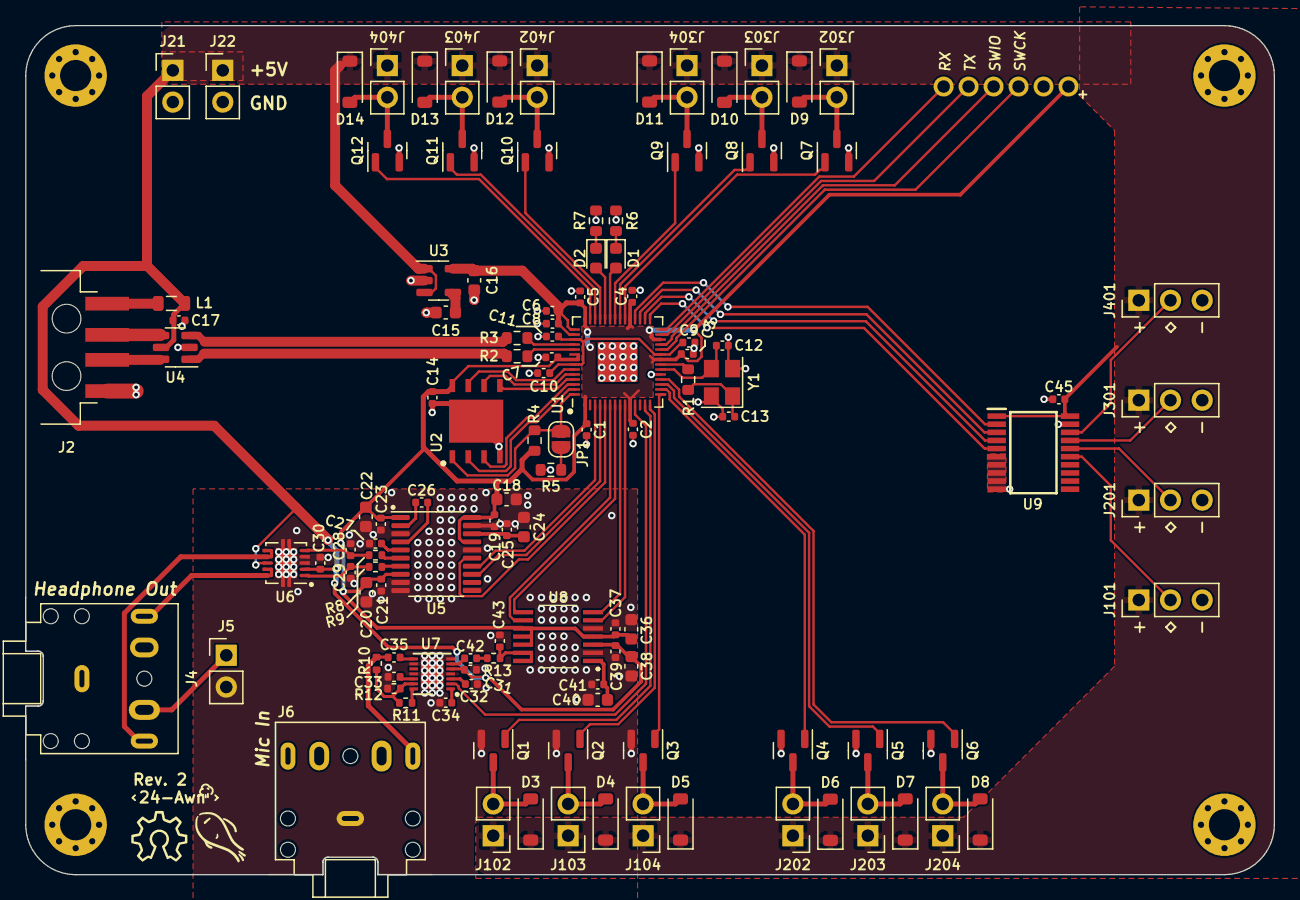
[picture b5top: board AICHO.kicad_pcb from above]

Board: 2 copper layers, 100.0 x 68.0 mm, 122 parts (0 on the bottom side), 92 nets.

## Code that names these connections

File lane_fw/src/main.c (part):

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}

  // ============ Pumps ============ //
  // PUMP_1 (Drain)   = PA0 AF13 = TIM1_CH3
  // PUMP_2 (Inflate) = PA1 AF13 = TIM1_CH4
  // PUMP_3 (Valve)   = PA2 AF13 = TIM3_CH1
{
  HAL_GPIO_Init(GPIOA, &(GPIO_InitTypeDef){
    .Mode = GPIO_MODE_AF_PP,
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}

  // ============ Pressure sensor ============ //
  // PA3 = ADC_IN3
  static ADC_HandleTypeDef adc1;
  uint32_t vrefint_value = 0;
{
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  });

  // ============ RS-485 UART ============ //
  // PA4 AF9 = UART2_TX
  // PA5 AF9 = UART2_RX
{
  HAL_GPIO_Init(GPIOA, &(GPIO_InitTypeDef){
    .Mode = GPIO_MODE_AF_PP,
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}

  // ============ Half-duplex UART ============ //
  // PA7 AF8 = UART1_TX
{
  HAL_GPIO_Init(GPIOA, &(GPIO_InitTypeDef){
    .Mode = GPIO_MODE_AF_PP,
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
